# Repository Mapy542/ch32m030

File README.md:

# RISC - V FOC BLDC & Stepper Driver

The latest version is the ch32v307drv project. I moved away from the original ch32m030 with integrated gate drivers because of the limited current and voltage capabilities. The ch32v307 has a much more MCU with embedded Ethernet phy. I'm hoping to use Ethernet to build a control system for my laser cutter with a homebrew motion controller board.

I am using the LMG2100 100V 53A GAN Totem pole packages from TI because they do all of the hard parts :P

The idea with all IO is to terminate into shielded rj-45 and use shielded cable. For the safety port, the opto-couplers exist to isolate ground loops with other boards in the cabinet, not user protection; hence the lack of creepage and clearance (<=100V). (Also, I needed area for the traces)

You can grab the datasheet if your curious, but I built a pinmux tool to make pin selection easier, and it gives a good overview of capabilities of the chip. It's the part of CubeMX I enjoy using... but with pin remap option automatic solving
[Ch32V307VCT6 Pin Mux Selection](https://bukoski.dev/tools/pinmux#project=lz%3AN4KABGBEBuCmBOBnAlgewHaQFxgIwBpwoBbWAFwENsxQIJJ0LTrIBjACwGYAmaTgBgDsAE3jRIhOlFbxYFMrGEBBMi279uANgC0-AKzbunACq49WTgA4suSwDpNuAJwAtCUXoBXAA7D5ilTUNHX4Qk35cG24bABYHfldIIgBfSShEWAAbWFYFYQARWAAzZHRkMjR0AElhFgB3Dm0OHj4haFydTIBHIu9cfn53elhiACNFYUVCkrKKjGp0T0zMtMhvBGRvdgQKTIBlSgVEagBtDxpz%2BnX4Te34XZqWfKUAYVwhqShYRlHs2pwyPBPLA0lJIBlsrlFAAlVCeCroADmAHlvHNqv8oJMihQlqpQXRIPA4QjES92KhkKxYABpUqYyC4sioJJSVLnWifNYbLY7TKPHCQZ4vbgfMHfCi-RTUQHAgn0CE5PKw%2BGlFFoyoCrHFXGZfGXKDE1VI8mU6l09AMpks87sqScsHXW58rWQACixgAEmLCRKpZjZSCDeCskqYSS1aj0a7sbr9Z9DRGTRSqbT6SxrT7hj8-ntkIjGPzhMccGcE-RoQANAByWcJVYACnX6MYa82oK2mwaALq2gkOwlO3n3IssZENpTveVfHPSgFAoMJkOQ5VJ9XRhmxvF1olr02pi1W%2BE2tn94NDu4PBnjpSi6eQP1-GUL%2B%2BKqHCFWkqOazc67f3o1SX3c100FTM%2Bw5c8eUvUdBRvTgd0fOcwEDV9Q3fT9Iw1DAYz-PUd0AtVgLTS0M2PVk6DtOgByuaCXWvCcYkQ2cAxfYM31XY11x-Fgt3wgC9xTEDSLA8iIPtKCbmHK8x2MABxAB9AAxPZmMlJ95zldj0M4r9sIxXi8PjLlCOTM0SKPZk1P9PMCyvEswDLctIAANQAIQAVVUntxOoyTnRHV1jCqABZKdgyQ1itKXDjwy478cN-HF-2DUyySEiyyKs%2B9ItswsagcpylxeT1wvLKAStwWtp3oEq7wNWrPW4aqGoqz0EJqtrOBa8rIDcmkqlrHzT0gpcL3olhgpCjqIpY59oq5WKPzXBKDMFPjjLBNLiMPLKWRyli8vs05WsgSr2zOpqLpKhDhsos8xrowKGSmpiDvU5DUO0lc4r0jdDOS-jUsE8zdtE7LZo%2B4QjqLQrTvOzrLvq3qbooqRexGiTHqkmCgtC-prI0lC2JinTfqw-71qMgiQYPUCoEzd6bPzfLixOlHSuu0qeuc-rBrRugMfu0auXG57JtCyxCc%2BknFrJ5b4v03DAc2wltoysGGfIpncxZ47S3hq67ogKiIBoqAxZkwU9gbKoZqXSL5sXOWfoVv6eKplWaa4nb6cZbXIeZuzYfZ5zqz2byEyFk2HtFp6rYqpRqzKrlHc052wSWzCkVW5W429oCNb98DMb87GAoTyAlHyF5paijPCSzlalcxRZlgEn2i5ErWIYdw69ZDg3esGgnEZHlOlxH5HnJH%2B2Z%2BTt7TpHvQBYgaOwFNi5y%2Bk2CoBUkLa515CcUyDI0Nd7PuMShYlhWYHO9B4uxNLs3-J3vGQqcOunfPsM3Ypj2YA253yXOrR%2B3d-a91Tv3YOBVQ7FU5ojOqq8wDr03ubbkOMJqCimtPcUc0cAnzPt9P%2Bl9c6t1vh3Qu4DLInmFljOOWDxY4NCivI%2BmIiENwVPLMhLcb7t3vtQumECS6USIN2VY3hSgHH8HDBhjpSiugbC8QY95UBwHgDcSYIVUCTD2juTIkosgsGgIiREAt0HnkUQyZRE9CTqIQFo2AOi9Hg32sGQx4xMgmNGJ4Y4vlX5jWsSwZReD7EaKcS42A%2Bj7yeOMYKTwFjY4KLWlAZRc8wQOM0cgbRujoluIMUY7xgo6hJJFikpRShVHBiyZEvJMSPFFJYAAD3GMQIoZT5GDmCYKCcdj6C1Jyc4%2BpBTYlNJKW0jpASt6ix6Wk28O5Bm5NcT3dxS44nFKgNASZnSy6zNSZACcGTwmOKGVEhp6zxlQE8Ds6ZGCpEHMYosiJZyRmrMKV4lgOSADWuzAn7MqWwmpLzln5PeWMz5gofl-JmRUmxShNDPNOaCi5XINksG%2BKwXAVA7lWMeUoQQSLskotGY0yFM4sWjBhfcuZhy3LVKXEs4ZKzIFrLRVch86AsUAC9qV4qUW6KWaiQXMrBayj58TrneNxUEx5bov7CuRaK1FYJ0UJL5bKgVo9gVKvOaSy55KYDSpfrC7pcrcD9KgEyvV4KyWSpgBqgFNi3S4DCQMkVNrxUQvtXUY19C9lwpCS6457rdVvK9XazZkBSkyqdUGswRK6kssZpGlgiBmTsEdYG3p%2BRXWJtecmgOBr7WYv4Dik1NLHm5pDVaj14aU3FqjaWqlsbs1pNzYvRldbC1QNVRy0tvLW1msqbgGtkBrX1qLeyw1Wbh02LcoixVxLlX6unfa2dVxaUNjckKnVy7PUNrXVGjdFst1uQVXupNYrD19pnUOzdcq3W1rDT2tlt77XptQH6mO5S51BrHRO19Eqo3NO-RvZJf6c2WvHd269U730gZPWsM9hKl1XpVYSNV6QACeXKkMPIFZ2rkgGxWIikagbQJJvDwmAywTIyBiAKXYApdN8h8NbrdECrtL7SPkco-Cajqt6BYcgPRxjmQWOHHY48l4RHMmwYw8Jjl6AyBYuk0ol4XHiMKdXQhlgKnWCinvaeg5blkTImMAy7TPGWBkbQNoUognaOCnUzYt4AGdNQDsxRxzNHvVRrEwpMDljNVudwHJk5%2B7w3eYc%2BgJz-m6MMaY65kJ%2BQL3cai0BhLgocToDAN4OoxAUtQegyRxTUARO5fy4VsAvnVDGeQ1W7VGX0OChi1RvzqawK5DAE%2BBrBGbH5F3S1gtvH7MdaExVjl9H0DfN69KW04iQDJCAA)

Here's the vector instruction set chip, but there's no stock of it yet:

[Ch32V467](https://bukoski.dev/tools/pinmux#project=lz%3AN4KABGBEBuCmBOBnAlgewHaQFxgIwBpwoBbWAFwENsxQIJJ0LTrIAhAGwvQGswBhABYBmAEwA1ACwA2AOyRCdKAGN4sCmVgATAIJkWIgAwipAWgOmDQgCoHcWXBKwBWABwA6XE4kAteUXoArgAOmupauvpGFhbWtvZO9rhuTjJSvkQAvgpQiLDssEoamgAisABmyOjIZGjoAJKaLADuSgImraLQ0jJwZKbsAI5lQbgGBn70sMQARlqaWqUVVTUY1OgB7OzZkEEIyEECCBTsAMqUGojUANoAuttBlWdhlzi3IBlAA)

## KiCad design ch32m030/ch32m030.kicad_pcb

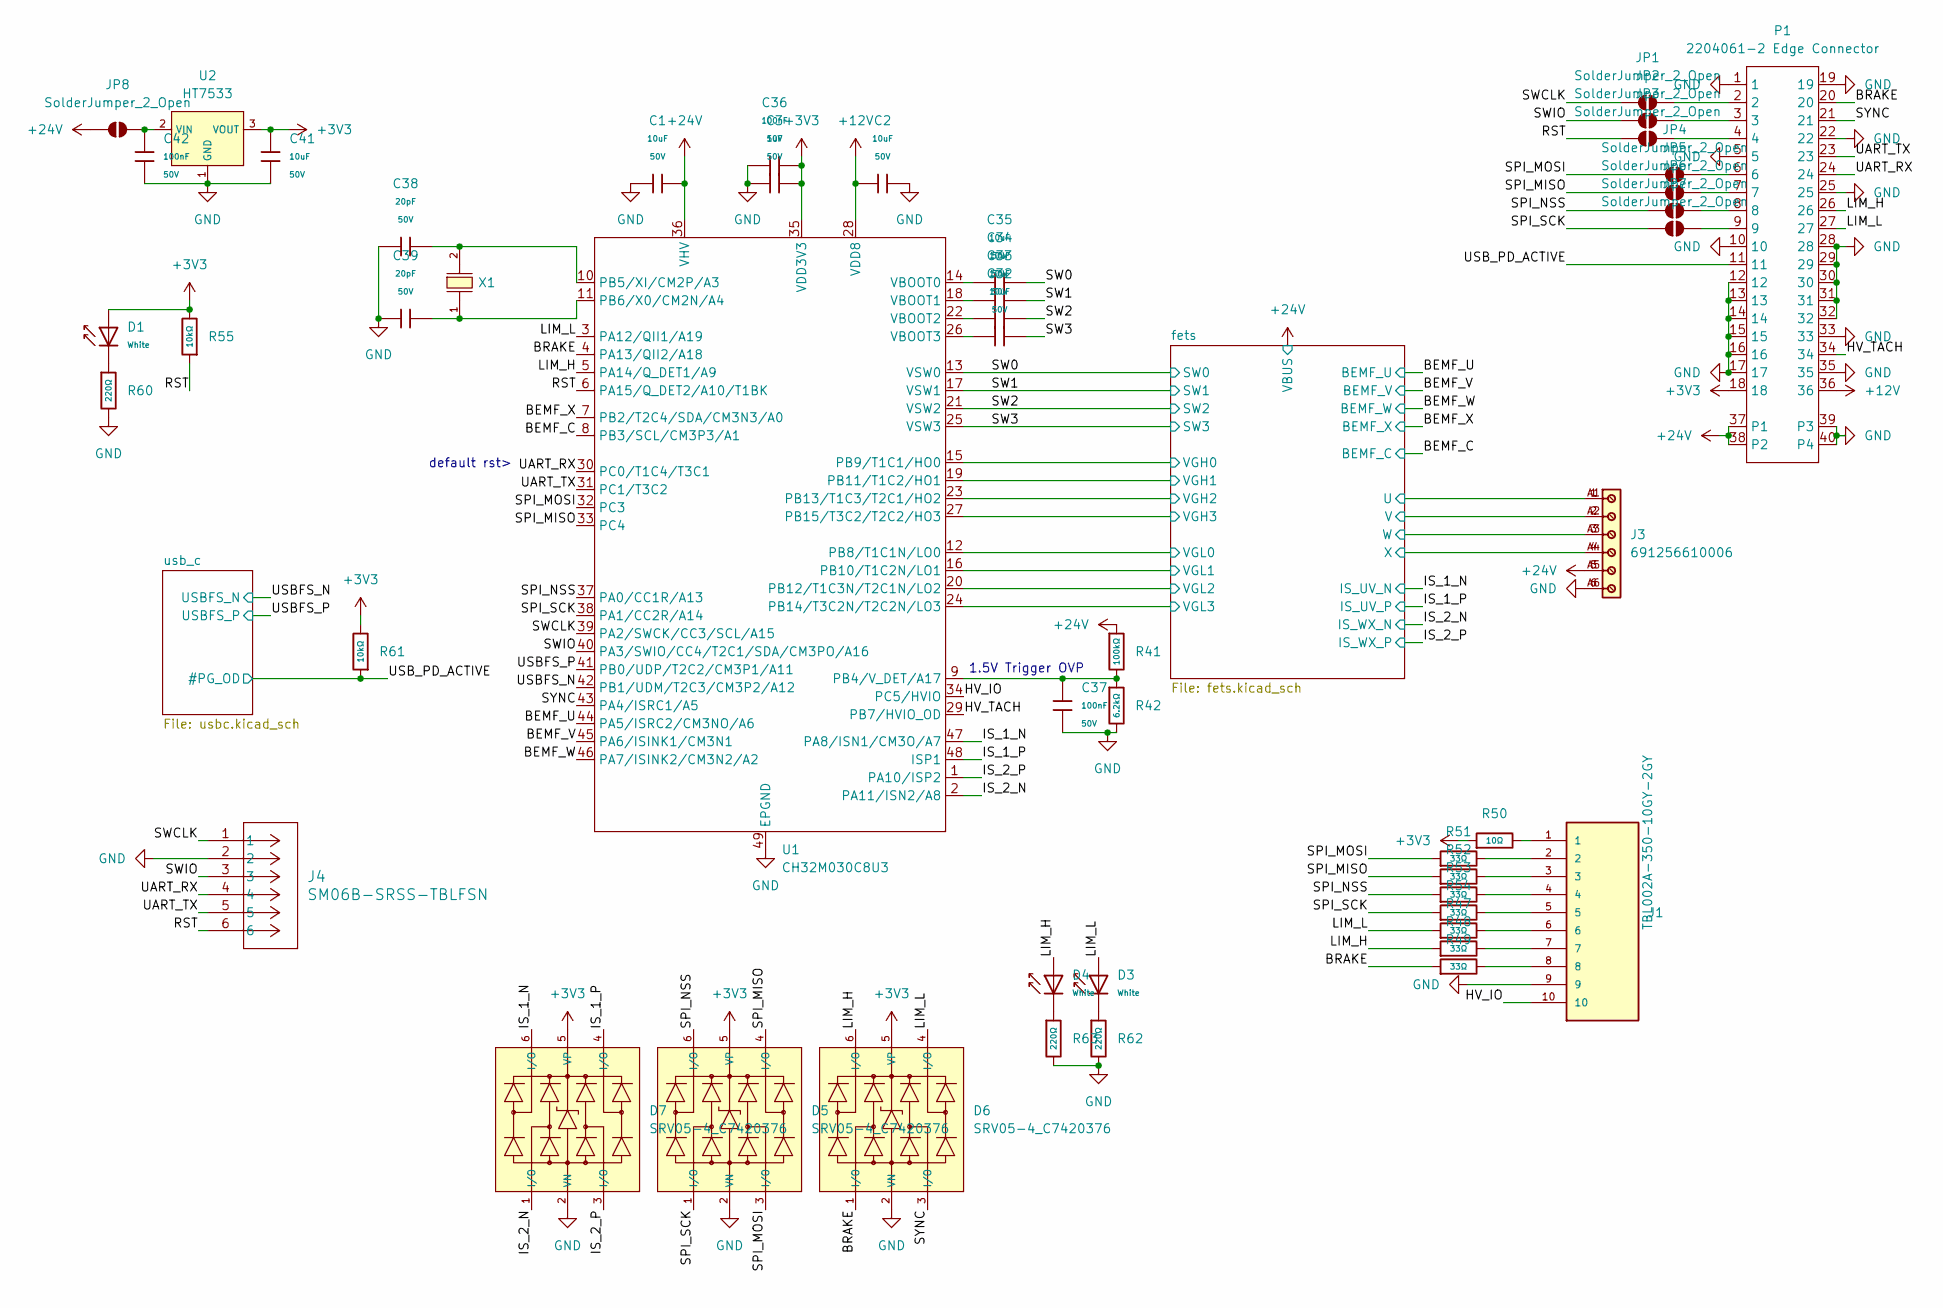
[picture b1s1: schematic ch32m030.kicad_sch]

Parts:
C1, C2, C32, C33, C34, C35, C41: 10uF; C_1206; Voltage Rated 50V; Tolerance ±10%; Part CL31A106KBHNNNE; LCSC C13585
C3: 1uF; C_0603; Voltage Rated 50V; Tolerance ±10%; Part CL10A105KB8NNNC; LCSC C15849
C36, C37, C42: 100nF; C_0603; Voltage Rated 50V; Tolerance ±10%; Part CC0603KRX7R9BB104; LCSC C14663
C38, C39: 20pF; C_0402; Voltage Rated 50V; Tolerance ±5%; Part 0402CG200J500NT; LCSC C1554
D1, D3, D4: White; D_0603; Part KT-0603W; LCSC C2290
D5, D6, D7: SRV05-4_C7420376; SOT-23-6_L2.9-W1.6-P0.95-LS2.8-BL-1; Breakdown Voltage (Vbr) 6V; Clamping Voltage@Ipp 12.5V; Part SRV05-4; LCSC C7420376
J1: TBL002A-350-10GY-2GY; CUI_TBL002A-350-10GY-2GY; PARTREV 1.0
J3: 691256610006
J4: SM06B-SRSS-TBLFSN; CONN_SM06B-SRSS-TB_JST
JP1, JP2, JP3, JP4, JP5, JP6, JP7, JP8: SolderJumper_2_Open; SolderJumper-2_P1.3mm_Open_TrianglePad1.0x1.5mm
P1: 2204061-2 Edge Connector; edge
R41: 100kΩ; R_0603; Overload Voltage (Max) 75V; Tolerance ±1%; Part 0603WAF1003T5E; LCSC C25803
R42: 6.2kΩ; R_0603; Overload Voltage (Max) 75V; Tolerance ±1%; Part 0603WAF6201T5E; LCSC C4260
R47, R48, R49, R51, R52, R53, R54: 33Ω; R_0603; Overload Voltage (Max) 75V; Tolerance ±1%; Part 0603WAF330JT5E; LCSC C23140
R50: 10Ω; R_0603; Overload Voltage (Max) 75V; Tolerance ±1%; Part 0603WAF100JT5E; LCSC C22859
R55, R61: 10kΩ; R_0603; Overload Voltage (Max) 75V; Tolerance ±1%; Part 0603WAF1002T5E; LCSC C25804
R60, R62, R63: 220Ω; R_0603; Overload Voltage (Max) 75V; Tolerance ±1%; Part 0603WAF2200T5E; LCSC C22962
U1: CH32M030C8U3; QFN-48-1EP_7x7mm_P0.5mm_EP3.5x3.5mm
U2: HT7533; SOT-89-3_L4.5-W2.5-P1.50-LS4.2-BR; Output Voltage 3.3V; Dropout Voltage 55mV@(1mA); Part HT7533-1; LCSC C14289
X1: X50328MSB2GI; CRYSTAL-SMD_L5.0-W3.2; Frequency Tolerance ±10ppm; Part X50328MSB2GI; LCSC C115962

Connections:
+3V3: C3.2, C36.2, C41.2, D1.2, D5.5 (VP), D6.5 (VP), D7.5 (VP), P1.18, R50.1, R55.2, R61.2, U1.35 (VDD3V3), U2.3 (VOUT); also elsewhere on the board
+12V: C2.1, P1.36, U1.28 (VDD8)
+24V: C1.1, J3.5, J3.A5, JP8.1 (A), P1.37 (P1), P1.38 (P2), R41.1, U1.36 (VHV); also elsewhere on the board
/BEMF_C: U1.8 (PB3/SCL/CM3P3/A1); also elsewhere on the board
/BEMF_U: U1.44 (PA5/ISRC2/CM3NO/A6); also elsewhere on the board
/BEMF_V: U1.45 (PA6/ISINK1/CM3N1); also elsewhere on the board
/BEMF_W: U1.46 (PA7/ISINK2/CM3N2/A2); also elsewhere on the board
/BEMF_X: U1.7 (PB2/T2C4/SDA/CM3N3/A0); also elsewhere on the board
/BRAKE: D6.1 (I/O), P1.20, R49.1, U1.4 (PA13/QII2/A18)
/HV_IO: J1.10, U1.34 (PC5/HVIO)
/HV_TACH: P1.34, U1.29 (PB7/HVIO_OD)
/IS_1_N: D7.6 (I/O), U1.47 (PA8/ISN1/CM3O/A7); also elsewhere on the board
/IS_1_P: D7.4 (I/O), U1.48 (ISP1); also elsewhere on the board
/IS_2_N: D7.1 (I/O), U1.2 (PA11/ISN2/A8); also elsewhere on the board
/IS_2_P: D7.3 (I/O), U1.1 (PA10/ISP2); also elsewhere on the board
/LIM_H: D4.2, D6.6 (I/O), P1.26, R48.1, U1.5 (PA14/Q_DET1/A9)
/LIM_L: D3.2, D6.4 (I/O), P1.27, R47.1, U1.3 (PA12/QII1/A19)
/RST: J4.6, JP3.1 (A), R55.1, U1.6 (PA15/Q_DET2/A10/T1BK)
/SPI_MISO: D5.4 (I/O), JP5.1 (A), R52.1, U1.33 (PC4)
/SPI_MOSI: D5.3 (I/O), JP4.1 (A), R51.1, U1.32 (PC3)
/SPI_NSS: D5.6 (I/O), JP6.1 (A), R53.1, U1.37 (PA0/CC1R/A13)
/SPI_SCK: D5.1 (I/O), JP7.1 (A), R54.1, U1.38 (PA1/CC2R/A14)
/SW0: C35.2, J3.1, J3.A1, U1.13 (VSW0); also elsewhere on the board
/SW1: C34.2, J3.2, J3.A2, U1.17 (VSW1); also elsewhere on the board
/SW2: C33.2, J3.3, J3.A3, U1.21 (VSW2); also elsewhere on the board
/SW3: C32.2, J3.4, J3.A4, U1.25 (VSW3); also elsewhere on the board
/SWCLK: J4.1, JP1.1 (A), U1.39 (PA2/SWCK/CC3/SCL/A15)
/SWIO: J4.3, JP2.1 (A), U1.40 (PA3/SWIO/CC4/T2C1/SDA/CM3PO/A16)
/SYNC: D6.3 (I/O), P1.21, U1.43 (PA4/ISRC1/A5)
/UART_RX: J4.4, P1.24, U1.30 (PC0/T1C4/T3C1)
/UART_TX: J4.5, P1.23, U1.31 (PC1/T3C2)
/USBFS_N: U1.42 (PB1/UDM/T2C3/CM3P2/A12); also elsewhere on the board
/USBFS_P: U1.41 (PB0/UDP/T2C2/CM3P1/A11); also elsewhere on the board
/USB_PD_ACTIVE: P1.11, R61.1; also elsewhere on the board
/fets/VGH0: U1.15 (PB9/T1C1/HO0); also elsewhere on the board
/fets/VGH1: U1.19 (PB11/T1C2/HO1); also elsewhere on the board
/fets/VGH2: U1.23 (PB13/T1C3/T2C1/HO2); also elsewhere on the board
/fets/VGH3: U1.27 (PB15/T3C2/T2C2/HO3); also elsewhere on the board
/fets/VGL0: U1.12 (PB8/T1C1N/LO0); also elsewhere on the board
/fets/VGL1: U1.16 (PB10/T1C2N/LO1); also elsewhere on the board
/fets/VGL2: U1.20 (PB12/T1C3N/T2C1N/LO2); also elsewhere on the board
/fets/VGL3: U1.24 (PB14/T3C2N/T2C2N/LO3); also elsewhere on the board
unnamed: D1.1, R60.1
unnamed: D3.1, R62.1
unnamed: D4.1, R63.1
unnamed: J1.1, R50.2
unnamed: J1.2, R51.2
unnamed: J1.3, R52.2
unnamed: J1.4, R53.2
unnamed: J1.5, R54.2
unnamed: J1.6, R47.2
unnamed: J1.7, R48.2
unnamed: J1.8, R49.2
unnamed: JP1.2 (B), P1.2
unnamed: JP2.2 (B), P1.3
unnamed: JP3.2 (B), P1.4
unnamed: JP4.2 (B), P1.6
unnamed: JP5.2 (B), P1.7
unnamed: JP6.2 (B), P1.8
unnamed: JP7.2 (B), P1.9
unnamed: C42.2, JP8.2 (B), U2.2 (VIN)
unnamed: C37.2, R41.2, R42.1, U1.9 (PB4/V_DET/A17)
unnamed: C38.2, U1.10 (PB5/XI/CM2P/A3), X1.2
unnamed: C39.2, U1.11 (PB6/X0/CM2N/A4), X1.1
unnamed: C35.1, U1.14 (VBOOT0)
unnamed: C34.1, U1.18 (VBOOT1)
unnamed: C33.1, U1.22 (VBOOT2)
unnamed: C32.1, U1.26 (VBOOT3)

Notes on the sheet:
1.5V Trigger OVP
default rst>

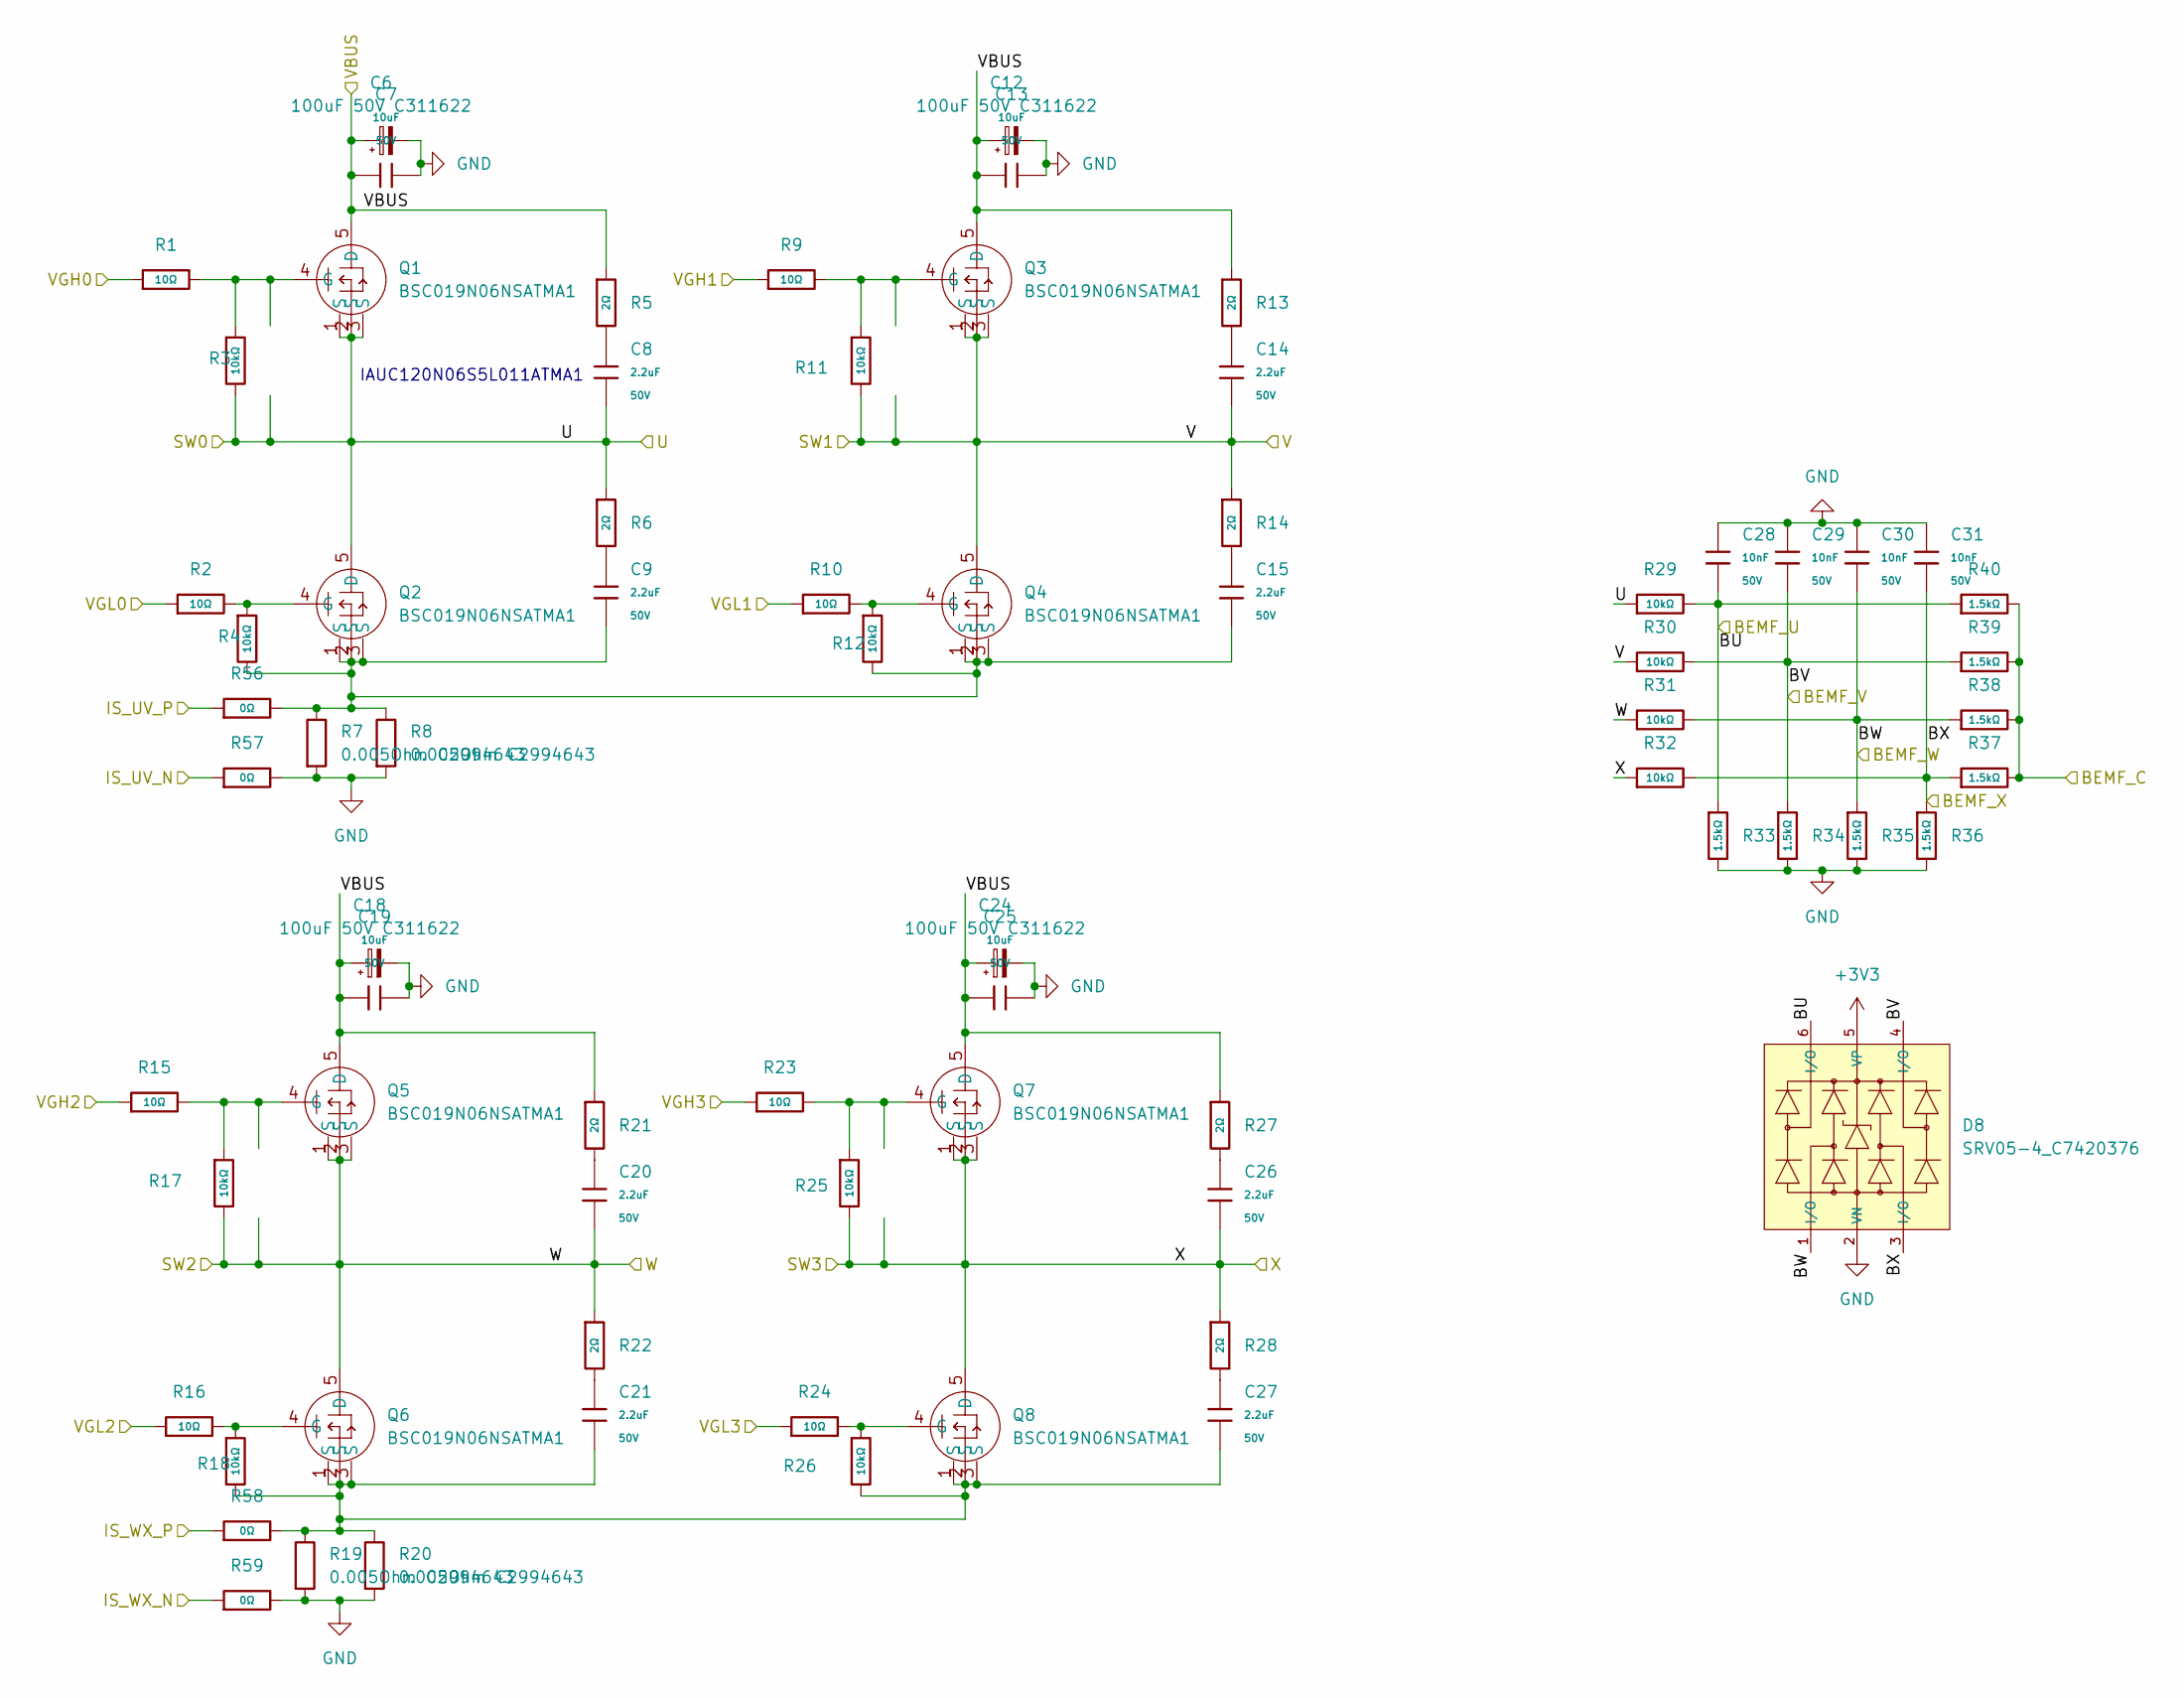
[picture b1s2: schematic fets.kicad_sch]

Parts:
C6, C12, C18, C24: 100uF 50V C311622; CP_Elec_6.3x7.7
C7, C13, C19, C25: 10uF; C_1206; Voltage Rated 50V; Tolerance ±10%; Part CL31A106KBHNNNE; LCSC C13585
C8, C9, C14, C15, C20, C21, C26, C27: 2.2uF; C_1206; Voltage Rated 50V; Tolerance ±10%; Part CL31B225KBHNNNE; LCSC C50254
C28, C29, C30, C31: 10nF; C_0603; Voltage Rated 50V; Tolerance ±10%; Part 0603B103K500NT; LCSC C57112
D8: SRV05-4_C7420376; SOT-23-6_L2.9-W1.6-P0.95-LS2.8-BL-1; Breakdown Voltage (Vbr) 6V; Clamping Voltage@Ipp 12.5V; Part SRV05-4; LCSC C7420376
Q1, Q2, Q3, Q4, Q5, Q6, Q7, Q8: BSC019N06NSATMA1; Infineon_PG-TDSON-8_6.15x5.15mm
R1, R2, R9, R10, R15, R16, R23, R24: 10Ω; R_0603; Overload Voltage (Max) 75V; Tolerance ±1%; Part 0603WAF100JT5E; LCSC C22859
R3, R4, R11, R12, R17, R18, R25, R26, R29, R30, R31, R32: 10kΩ; R_0603; Overload Voltage (Max) 75V; Tolerance ±1%; Part 0603WAF1002T5E; LCSC C25804
R5, R6, R13, R14, R21, R22, R27, R28: 2Ω; R_0603; Overload Voltage (Max) 75V; Tolerance ±1%; Part 0603WAF200KT5E; LCSC C22977
R7, R8, R19, R20: 0.005Ohm C2994643; R_2512_6332Metric
R33, R34, R35, R36, R37, R38, R39, R40: 1.5kΩ; R_0603; Overload Voltage (Max) 75V; Tolerance ±1%; Part 0603WAF1501T5E; LCSC C22843
R56, R57, R58, R59: 0Ω; R_0603; Overload Voltage (Max) 75V; Tolerance ±1%; Part 0603WAF0000T5E; LCSC C21189

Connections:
+3V3: D8.5 (VP); also elsewhere on the board
+24V: C6.1, C7.1, C12.1, C13.1, C18.1, C19.1, C24.1, C25.1, Q1.5 (D), Q3.5 (D), Q5.5 (D), Q7.5 (D), R5.1, R13.1, R21.1, R27.1; also elsewhere on the board
/BEMF_C: R37.2, R38.2, R39.2, R40.2; also elsewhere on the board
/BEMF_U: C28.2, D8.6 (I/O), R29.2, R33.1, R40.1; also elsewhere on the board
/BEMF_V: C29.2, D8.4 (I/O), R30.2, R34.1, R39.1; also elsewhere on the board
/BEMF_W: C30.2, D8.1 (I/O), R31.2, R35.1, R38.1; also elsewhere on the board
/BEMF_X: C31.2, D8.3 (I/O), R32.2, R36.1, R37.1; also elsewhere on the board
/IS_1_N: R57.1; also elsewhere on the board
/IS_1_P: R56.1; also elsewhere on the board
/IS_2_N: R59.1; also elsewhere on the board
/IS_2_P: R58.1; also elsewhere on the board
/SW0: C8.2, Q1.1 (S), Q1.2 (S), Q1.3 (S), Q2.5 (D), R3.2, R6.1, R29.1; also elsewhere on the board
/SW1: C14.2, Q3.1 (S), Q3.2 (S), Q3.3 (S), Q4.5 (D), R11.2, R14.1, R30.1; also elsewhere on the board
/SW2: C20.2, Q5.1 (S), Q5.2 (S), Q5.3 (S), Q6.5 (D), R17.2, R22.1, R31.1; also elsewhere on the board
/SW3: C26.2, Q7.1 (S), Q7.2 (S), Q7.3 (S), Q8.5 (D), R25.2, R28.1, R32.1; also elsewhere on the board
/fets/VGH0: R1.1; also elsewhere on the board
/fets/VGH1: R9.1; also elsewhere on the board
/fets/VGH2: R15.1; also elsewhere on the board
/fets/VGH3: R23.1; also elsewhere on the board
/fets/VGL0: R2.1; also elsewhere on the board
/fets/VGL1: R10.1; also elsewhere on the board
/fets/VGL2: R16.1; also elsewhere on the board
/fets/VGL3: R24.1; also elsewhere on the board
unnamed: C8.1, R5.2
unnamed: C9.1, R6.2
unnamed 44: C9.2, C15.2, Q2.1 (S), Q2.2 (S), Q2.3 (S), Q4.1 (S), Q4.2 (S), Q4.3 (S), R4.2, R7.1, R8.1, R12.2, R56.2; also elsewhere on the board
unnamed: C14.1, R13.2
unnamed: C15.1, R14.2
unnamed 47: C21.2, C27.2, Q6.1 (S), Q6.2 (S), Q6.3 (S), Q8.1 (S), Q8.2 (S), Q8.3 (S), R18.2, R19.1, R20.1, R26.2, R58.2; also elsewhere on the board
unnamed: C20.1, R21.2
unnamed: C21.1, R22.2
unnamed: C26.1, R27.2
unnamed: C27.1, R28.2
unnamed 74: Q1.4 (G), R1.2, R3.1; also elsewhere on the board
unnamed 75: Q2.4 (G), R2.2, R4.1; also elsewhere on the board
unnamed 76: Q3.4 (G), R9.2, R11.1; also elsewhere on the board
unnamed 77: Q4.4 (G), R10.2, R12.1; also elsewhere on the board
unnamed 78: Q5.4 (G), R15.2, R17.1; also elsewhere on the board
unnamed 79: Q6.4 (G), R16.2, R18.1; also elsewhere on the board
unnamed 80: Q7.4 (G), R23.2, R25.1; also elsewhere on the board
unnamed 81: Q8.4 (G), R24.2, R26.1; also elsewhere on the board

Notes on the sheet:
IAUC120N06S5L011ATMA1

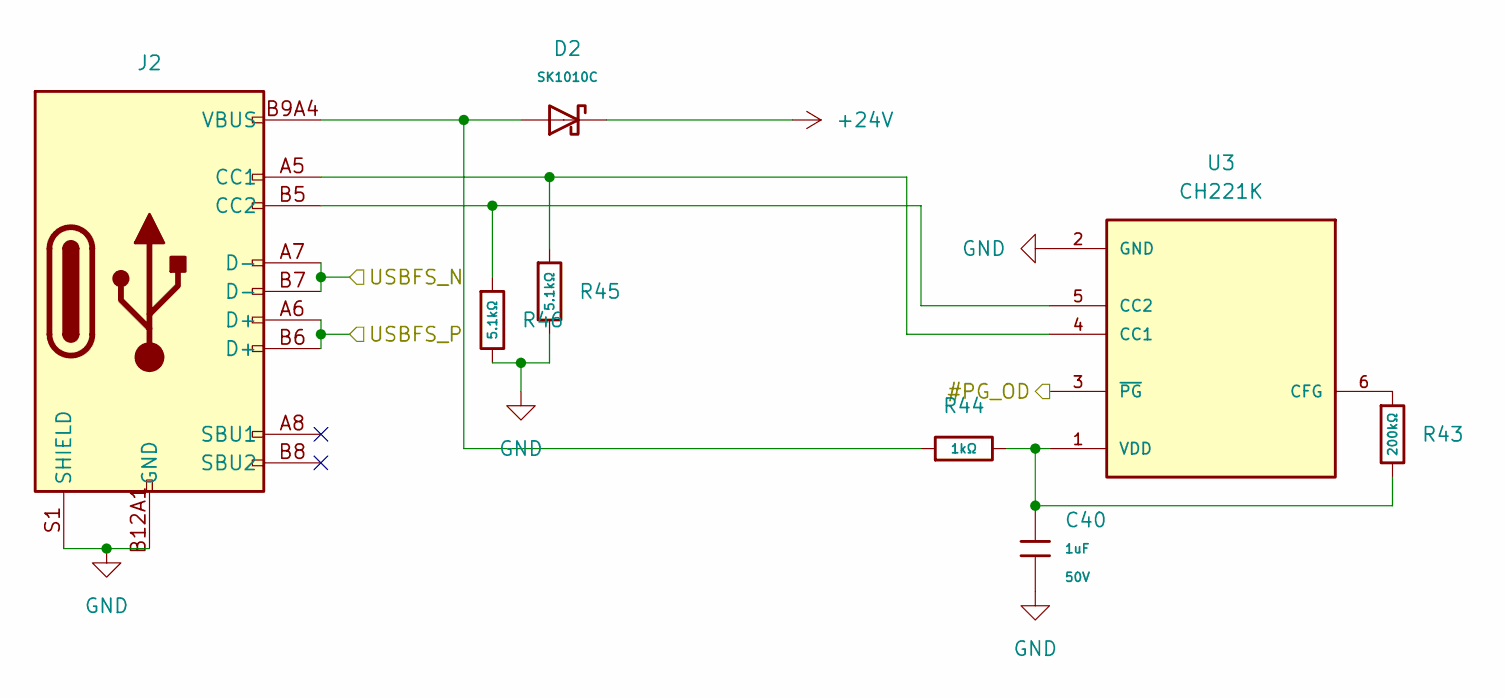
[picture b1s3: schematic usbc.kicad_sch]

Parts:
C40: 1uF; C_0603; Voltage Rated 50V; Tolerance ±10%; Part CL10A105KB8NNNC; LCSC C15849
D2: SK1010C; D_SMC; Forward Voltage (Vf@If) 850mV@10A; Reverse Voltage (Vr) 100V; Part SK1010C; LCSC C18199193
J2: Connector, USB-TYPE-C-16P; TYPE-C-SMD_HX-TYPE-C-16PIN; LCSC C2927039
R43: 200kΩ; R_0603; Overload Voltage (Max) 75V; Tolerance ±1%; Part 0603WAF2003T5E; LCSC C25811
R44: 1kΩ; R_0603; Overload Voltage (Max) 75V; Tolerance ±1%; Part 0603WAF1001T5E; LCSC C21190
R45, R46: 5.1kΩ; R_0603; Overload Voltage (Max) 75V; Tolerance ±1%; Part 0603WAF5101T5E; LCSC C23186
U3: CH221K; SOT95P280X120-6N; PARTREV 2.1

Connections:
+24V: D2.1; also elsewhere on the board
/USBFS_N: J2.A7 (D-), J2.B7 (D-); also elsewhere on the board
/USBFS_P: J2.A6 (D+), J2.B6 (D+); also elsewhere on the board
/USB_PD_ACTIVE: U3.3 (~PG); also elsewhere on the board
unnamed: D2.2, J2.A9B4 (VBUS), J2.B9A4 (VBUS), R44.1
unnamed: J2.A5 (CC1), R45.1, U3.4 (CC1)
unnamed: J2.B5 (CC2), R46.1, U3.5 (CC2)
unnamed: R43.1, U3.6 (CFG)
unnamed: C40.2, R43.2, R44.2, U3.1 (VDD)

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
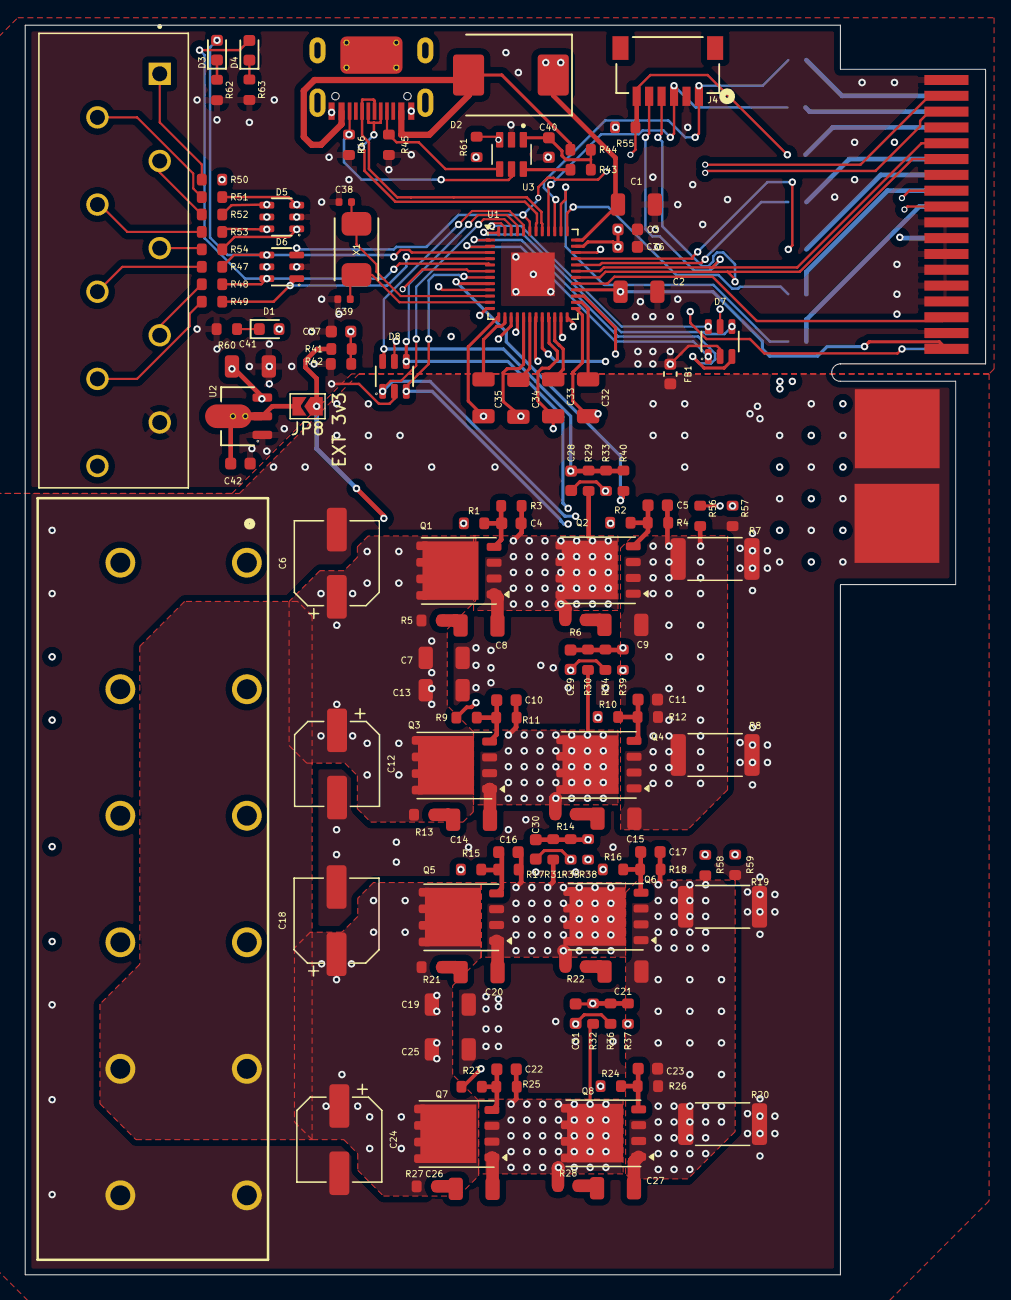
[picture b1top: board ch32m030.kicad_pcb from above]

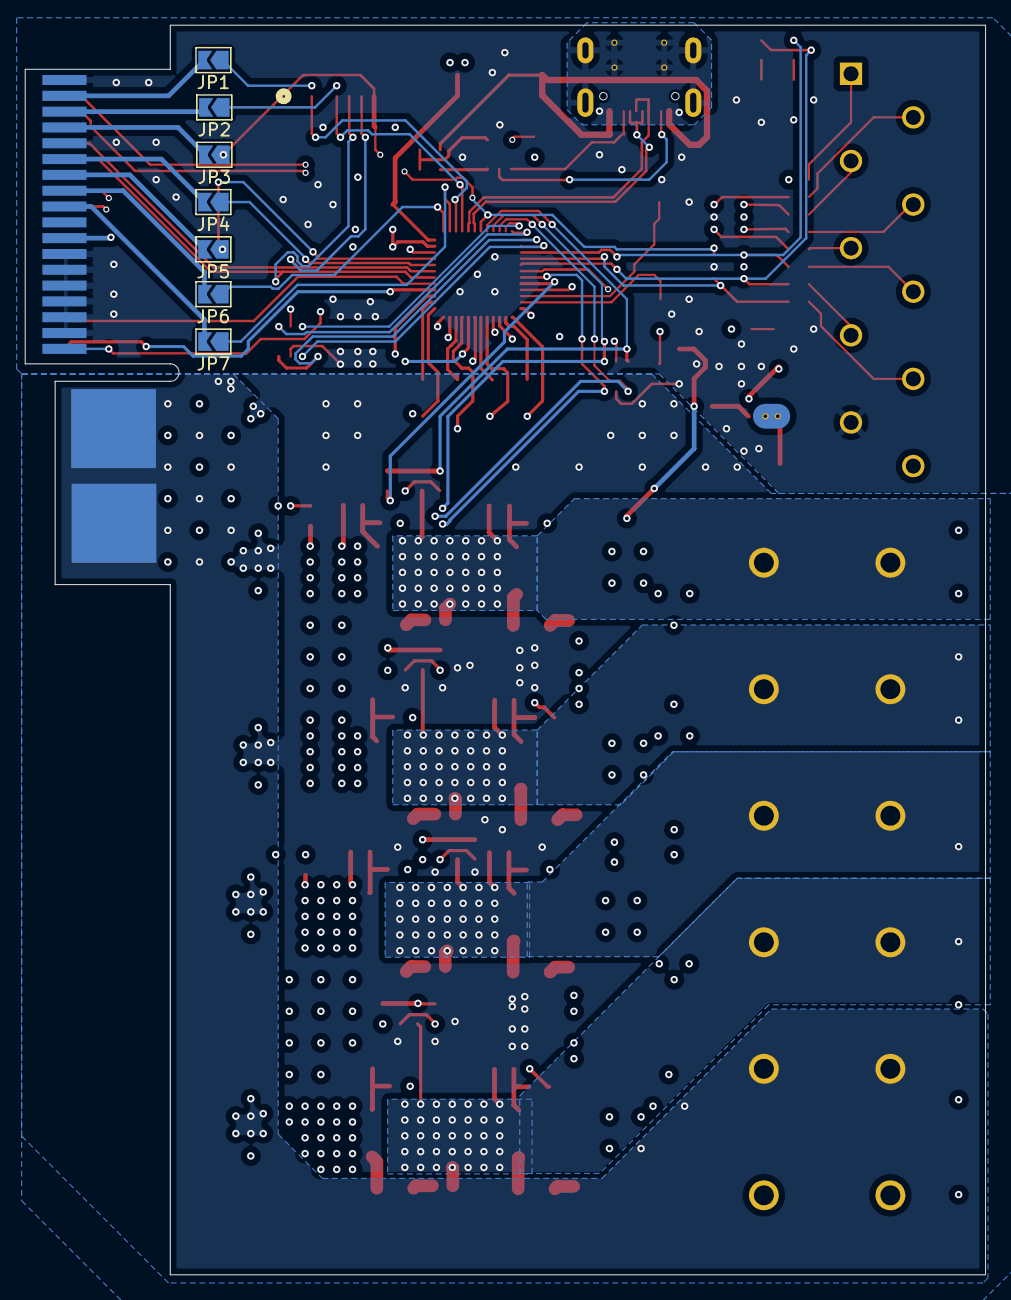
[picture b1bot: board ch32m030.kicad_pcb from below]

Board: 4 copper layers, 77.1 x 100.3 mm, 139 parts (7 on the bottom side), 93 nets.

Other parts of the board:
C4, C5, C10, C11, C16, C17, C22, C23: 1uF; C_0603
FB1: FB_0603

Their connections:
/SW0: C4.2; also elsewhere on the board
/SW1: C10.2; also elsewhere on the board
/SW2: C16.2; also elsewhere on the board
/SW3: C22.2; also elsewhere on the board
unnamed 44: C5.2, C11.2; also elsewhere on the board
unnamed 47: C17.2, C23.2; also elsewhere on the board
unnamed 74: C4.1; also elsewhere on the board
unnamed 75: C5.1; also elsewhere on the board
unnamed 76: C10.1; also elsewhere on the board
unnamed 77: C11.1; also elsewhere on the board
unnamed 78: C16.1; also elsewhere on the board
unnamed 79: C17.1; also elsewhere on the board
unnamed 80: C22.1; also elsewhere on the board
unnamed 81: C23.1; also elsewhere on the board
